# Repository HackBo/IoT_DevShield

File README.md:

# A Developement Shield for IoT proyects

A shield that include Sensors, Actuators And Comm Modules 'ready to work'.

The shield use the 'Arduino Socket' that accomplish the compatibility not only with Arduino boards also many other boards that use the 
same 'Arduino Socket' form.

The list of the actual components are:

## Sensors
 
 * MMA8452Q (Accelerometer)
 * LM35 (Temperature)
 * DHT11* (Humidity And Temperature)
 * SS39AT (Hall Effect)
 * SS351AT (Hall Effect)
 * LDR (Light)
 * Potenciometer
 * Switch

## Actuators

 * RGB LED
 * Buzzer
 * Rele
 * High Power Mosfet
 * Servo Motor*
 * LCD OLED*

## COMM Modules

 * HC05 (Bluetooth)
 * TSOP(IR Rx)
 * IR LED (IR Tx)
 * ESP-01* (WiFi)
 * NRF24L01+* (2.4GHz RF)

## Others

 * 24LC256 (EEPROM 256Kb)
 * DS1307 (RTC)

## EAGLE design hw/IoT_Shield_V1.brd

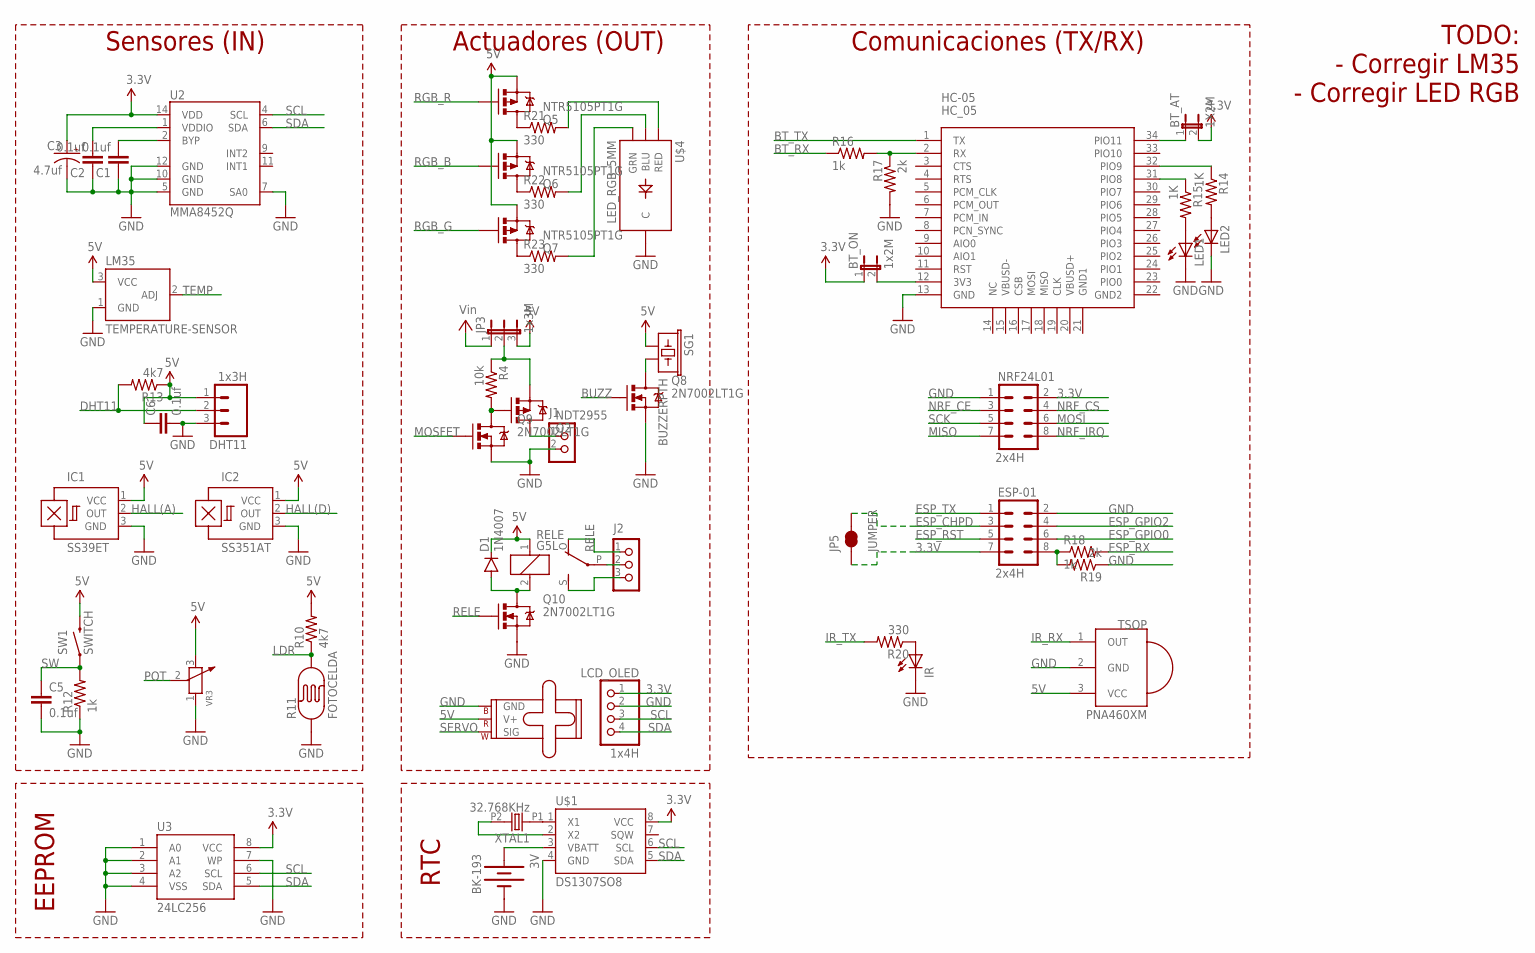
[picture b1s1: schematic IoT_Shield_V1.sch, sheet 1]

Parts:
3V: BK-193; BATTERY-20MMTH
BT_AT: 1X2M; JP1
BT_ON: 1x2M; JP1
C1, C2, C5, C6: 0.1uf; 0805
C3: 4.7uf; EIA3528-KIT
D1: 1N4007; SMA-DIODE
DHT11: 1x3H; 1X03_LOCK
ESP-01: 2x4H; 2X4
HC-05: HC_05; BLUETOOTH_SMD
IC1: SS39ET; SOT23-W
IC2: SS351AT; SOT23-W
IR: LEDIRL80A; IRL80A
J1: CON_TERMINAL_BLOCK_02-5MM; TERMINAL_BLOCK_2P_5
J2: CON_TERMINAL_BLOCK_03-5MM; TERMINAL_BLOCK_3P_5
JP3: 1x3M; JP2
JP5: JUMPER; PAD-JUMPER-2-NC_BY_TRACE_NO_SILK
LCD_OLED: 1x4H; 1X04
LED1, LED2: LEDCHIPLED_0805; CHIPLED_0805
LM35: TEMPERATURE-SENSOR; TO-92
NRF24L01: 2x4H; 2X4
Q2: NDT2955; SOT223
Q5, Q6, Q7: NTR5105PT1G; SOT23-3
Q8, Q9, Q10: 2N7002LT1G; SOT23-3
R4: 10k; 0805
R10, R13: 4k7; 0805
R11: FOTOCELDA; PHOTOCELL
R12, R16, R18: 1k; 0805
R14, R15: 1K; 0805
R17, R19: 2k; 0805
R20, R21, R22, R23: 330; 1206
RELE: G5L; G5LE
SERVO: 1X3M; 1X03
SG1: BUZZERPTH; BUZZER-12MM
SW1: SWITCH; TACTILE-PTH
TSOP: PNA460XM
U2: MMA8452Q; QFN-16_0.5MM
U3: 24LC256; SO08
U$1: DS1307SO8; SO08
U$4: LED_RGB_5MM; LED_PIRANHA_5MM
VR3: RES-ADJ'WH121-1'; ADJR2+3P-16.0X12.0X18.0MM
XTAL1: 32.768KHz; TC-26

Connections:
3.3V: BT_AT.2, BT_ON.1, C3.A (+), ESP-01.7, JP5.1, LCD_OLED.1, NRF24L01.2, U2.14 (VDD), U3.8 (VCC), U$1.8 (VCC); also elsewhere on the board
5V: C6.1, D1.C, DHT11.1, IC1.1 (VCC), IC2.1 (VCC), JP3.3, LM35.3 (VCC), Q5.2 (S), Q6.2 (S), Q7.2 (S), R10.2, R13.1, RELE.1, SERVO.2 (V+), SG1.+ (1), SW1.3 (2), TSOP.3 (VCC), VR3.3; also elsewhere on the board
BT_RX: R16.1; also elsewhere on the board
BT_TX: HC-05.1 (TX); also elsewhere on the board
BUZZ: Q8.1 (G); also elsewhere on the board
DHT11: DHT11.2, R13.2; also elsewhere on the board
ESP_CHPD: ESP-01.3, JP5.2; also elsewhere on the board
ESP_GPIO0: ESP-01.6; also elsewhere on the board
ESP_GPIO2: ESP-01.4; also elsewhere on the board
ESP_RST: ESP-01.5; also elsewhere on the board
ESP_RX: R18.2; also elsewhere on the board
ESP_TX: ESP-01.1; also elsewhere on the board
GND: 3V.P1- (-), C1.1, C2.1, C3.C (-), C5.2, C6.2, DHT11.3, ESP-01.2, HC-05.13 (GND), IC1.3 (GND), IC2.3 (GND), IR.K (C), J1.2, LCD_OLED.2, LED1.C, LED2.C, LM35.1 (GND), NRF24L01.1, Q8.2 (S), Q9.2 (S), Q10.2 (S), R11.1, R12.1, R17.2, R19.1, SERVO.3 (GND), TSOP.2 (GND), U2.5 (GND), U2.7 (SA0), U2.10 (GND), U2.12 (GND), U3.1 (A0), U3.2 (A1), U3.3 (A2), U3.4 (VSS), U3.7 (WP), U$1.4 (GND), U$4.- (C), VR3.1; also elsewhere on the board
HALL(A): IC1.2 (OUT); also elsewhere on the board
HALL(D): IC2.2 (OUT); also elsewhere on the board
IR_RX: TSOP.1 (OUT); also elsewhere on the board
IR_TX: R20.2; also elsewhere on the board
LDR: R10.1, R11.2; also elsewhere on the board
MISO: NRF24L01.7; also elsewhere on the board
MOSFET: Q9.1 (G); also elsewhere on the board
MOSI: NRF24L01.6; also elsewhere on the board
unnamed: U$1.2 (X2), XTAL1.P2 (2)
unnamed: U$1.1 (X1), XTAL1.P1 (1)
unnamed: 3V.P2+ (+), 3V.P3+ (+), U$1.3 (VBATT)
unnamed: C1.2, U2.2 (BYP)
unnamed: C2.2, U2.1 (VDDIO)
unnamed: J1.1, Q2.2 (D), Q2.4 (D)
unnamed: Q8.3 (D), SG1.- (2)
unnamed: Q2.1 (G), Q9.3 (D), R4.2
unnamed: D1.A, Q10.3 (D), RELE.2
unnamed: R23.2, U$4.G (GRN)
unnamed: R22.2, U$4.B (BLU)
unnamed: R21.2, U$4.R (RED)
unnamed: JP3.2, Q2.3 (S), R4.1
unnamed: BT_ON.2, HC-05.12 (3V3)
unnamed: HC-05.32 (PIO9), R14.1
unnamed: HC-05.31 (PIO8), R15.1
unnamed: LED1.A, R15.2
unnamed: LED2.A, R14.2
unnamed: HC-05.2 (RX), R16.2, R17.1
unnamed: ESP-01.8, R18.1, R19.2
unnamed: Q5.3 (D), R21.1
unnamed: BT_AT.1, HC-05.34 (PIO11)
unnamed: Q6.3 (D), R22.1
unnamed: Q7.3 (D), R23.1
unnamed: IR.A, R20.1
NRF_CE: NRF24L01.3; also elsewhere on the board
NRF_CS: NRF24L01.4; also elsewhere on the board
NRF_IRQ: NRF24L01.8
POT: VR3.2; also elsewhere on the board
RELE: Q10.1 (G); also elsewhere on the board
RELE_COMM: J2.2, RELE.P
RELE_NC: J2.1, RELE.O
RELE_NO: J2.3, RELE.S
RGB_B: Q6.1 (G); also elsewhere on the board
RGB_G: Q7.1 (G); also elsewhere on the board
RGB_R: Q5.1 (G); also elsewhere on the board
SCK: NRF24L01.5; also elsewhere on the board
SCL: LCD_OLED.3, U2.4 (SCL), U3.6 (SCL), U$1.6 (SCL); also elsewhere on the board
SDA: LCD_OLED.4, U2.6 (SDA), U3.5 (SDA), U$1.5 (SDA); also elsewhere on the board
SERVO: SERVO.1 (SIG); also elsewhere on the board
SW: C5.1, R12.2, SW1.1; also elsewhere on the board
TEMP: LM35.2 (ADJ); also elsewhere on the board
VIN: JP3.1; also elsewhere on the board

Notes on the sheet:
Sensores (IN)
Actuadores (OUT)
Comunicaciones (TX/RX)
RTC
EEPROM
TODO: - Corregir LM35 - Corregir LED RGB

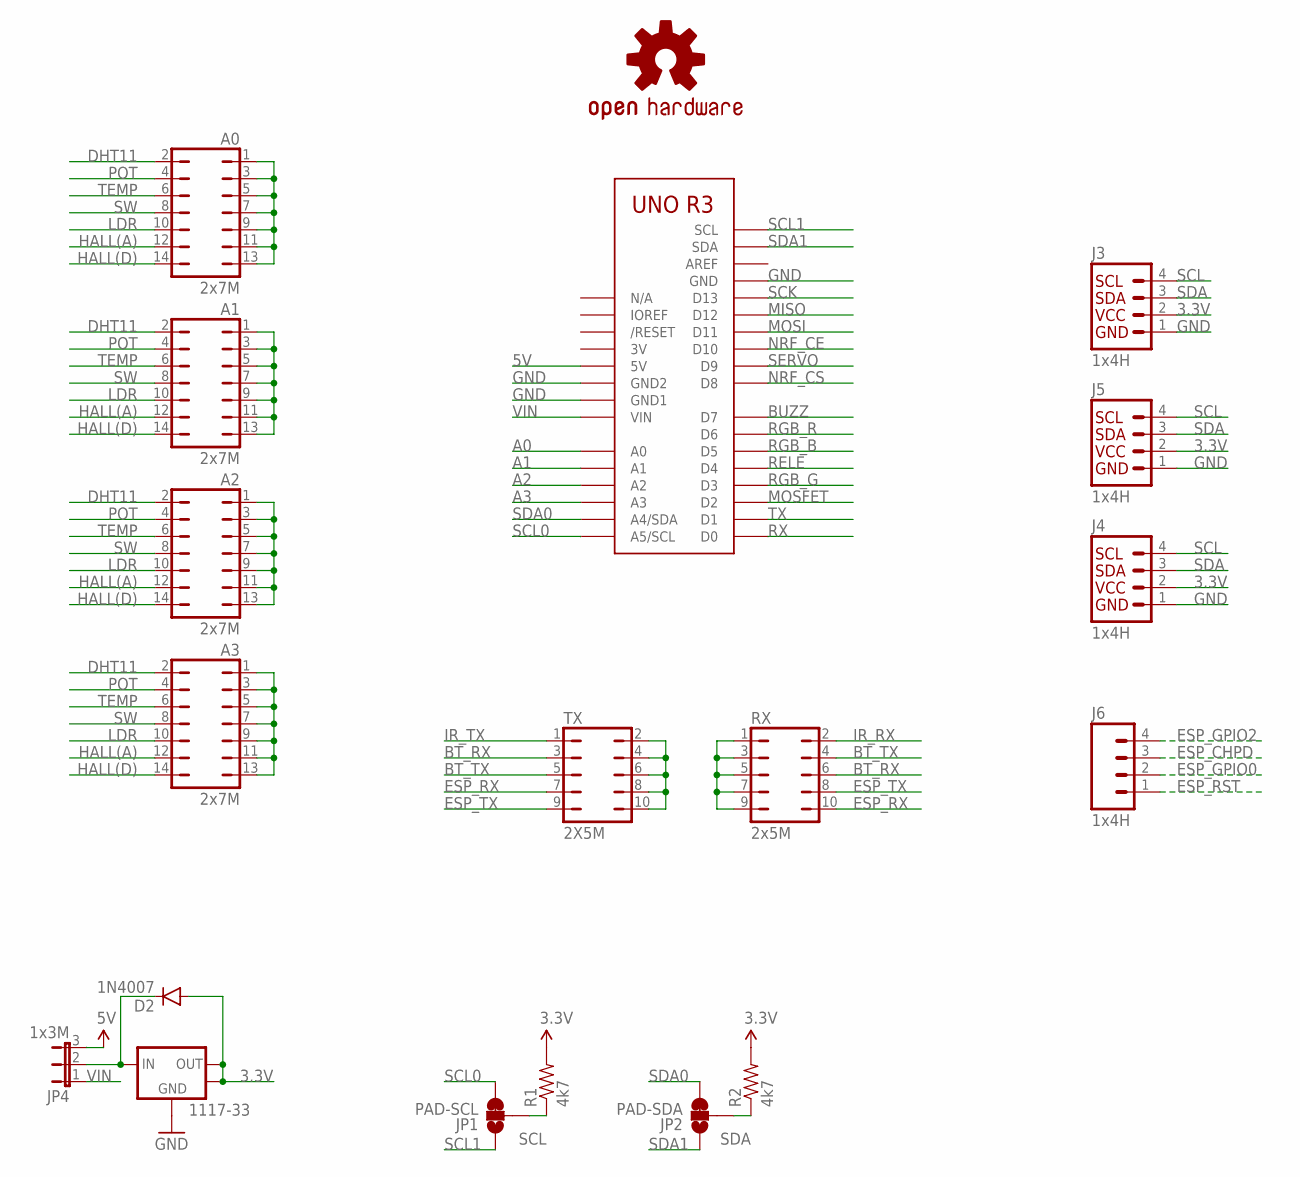
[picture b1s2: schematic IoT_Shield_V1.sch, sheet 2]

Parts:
1117-33: LV1117-33TO252; TO252
A0, A1, A2, A3: 2x7M; JP7Q
D2: 1N4007; SMA-DIODE
J3, J4, J5: 1x4H; 1X04
J6: 1x4H; 1X04_LOCK
JP1: PAD-SCL; PAD-JUMPER-3-2OF3_NC_BY_TRACE_YES_SILK_LARGE
JP2: PAD-SDA; PAD-JUMPER-3-2OF3_NC_BY_TRACE_YES_SILK_LARGE
JP4: 1x3M; JP2
LOGO1: OSHW-LOGOL-COPPER; OSHW-LOGO-L_COPPER
R1, R2: 4k7; 0805
RX: 2x5M; JP5Q
TX: 2X5M; JP5Q
U1: ARDUINOR3-DIMENSION; ARDUINOR3

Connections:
3.3V: 1117-33.2 (OUT), 1117-33.4 (OUT), D2.A, J3.2, J4.2, J5.2, R1.2, R2.2; also elsewhere on the board
3V: U1.3V
5V: JP4.3, U1.5V; also elsewhere on the board
A0: A0.1, A0.3, A0.5, A0.7, A0.9, A0.11, A0.13, U1.A0
A1: A1.1, A1.3, A1.5, A1.7, A1.9, A1.11, A1.13, U1.A1
A2: A2.1, A2.3, A2.5, A2.7, A2.9, A2.11, A2.13, U1.A2
A3: A3.1, A3.3, A3.5, A3.7, A3.9, A3.11, A3.13, U1.A3
BT_RX: RX.6, TX.3; also elsewhere on the board
BT_TX: RX.4, TX.5; also elsewhere on the board
BUZZ: U1.D7; also elsewhere on the board
DHT11: A0.2, A1.2, A2.2, A3.2; also elsewhere on the board
ESP_CHPD: J6.3; also elsewhere on the board
ESP_GPIO0: J6.2; also elsewhere on the board
ESP_GPIO2: J6.4; also elsewhere on the board
ESP_RST: J6.1; also elsewhere on the board
ESP_RX: RX.10, TX.7; also elsewhere on the board
ESP_TX: RX.8, TX.9; also elsewhere on the board
GND: 1117-33.1 (ADJ), J3.1, J4.1, J5.1, U1.GND, U1.GND1, U1.GND2; also elsewhere on the board
HALL(A): A0.12, A1.12, A2.12, A3.12; also elsewhere on the board
HALL(D): A0.14, A1.14, A2.14, A3.14; also elsewhere on the board
IR_RX: RX.2; also elsewhere on the board
IR_TX: TX.1; also elsewhere on the board
LDR: A0.10, A1.10, A2.10, A3.10; also elsewhere on the board
MISO: U1.D12; also elsewhere on the board
MOSFET: U1.D2; also elsewhere on the board
MOSI: U1.D11; also elsewhere on the board
unnamed: 1117-33.3 (IN), D2.C, JP4.2
NRF_CE: U1.D10; also elsewhere on the board
NRF_CS: U1.D8; also elsewhere on the board
POT: A0.4, A1.4, A2.4, A3.4; also elsewhere on the board
RELE: U1.D4; also elsewhere on the board
RGB_B: U1.D5; also elsewhere on the board
RGB_G: U1.D3; also elsewhere on the board
RGB_R: U1.D6; also elsewhere on the board
RX: RX.1, RX.3, RX.5, RX.7, RX.9, U1.D0
SCK: U1.D13; also elsewhere on the board
SCL: J3.4, J4.4, J5.4, JP1.2, R1.1; also elsewhere on the board
SCL0: JP1.3, U1.A5 (A5/SCL)
SCL1: JP1.1, U1.SCL
SDA: J3.3, J4.3, J5.3, JP2.2, R2.1; also elsewhere on the board
SDA0: JP2.3, U1.A4 (A4/SDA)
SDA1: JP2.1, U1.SDA
SERVO: U1.D9; also elsewhere on the board
SW: A0.8, A1.8, A2.8, A3.8; also elsewhere on the board
TEMP: A0.6, A1.6, A2.6, A3.6; also elsewhere on the board
TX: TX.2, TX.4, TX.6, TX.8, TX.10, U1.D1
VIN: JP4.1, U1.VIN; also elsewhere on the board

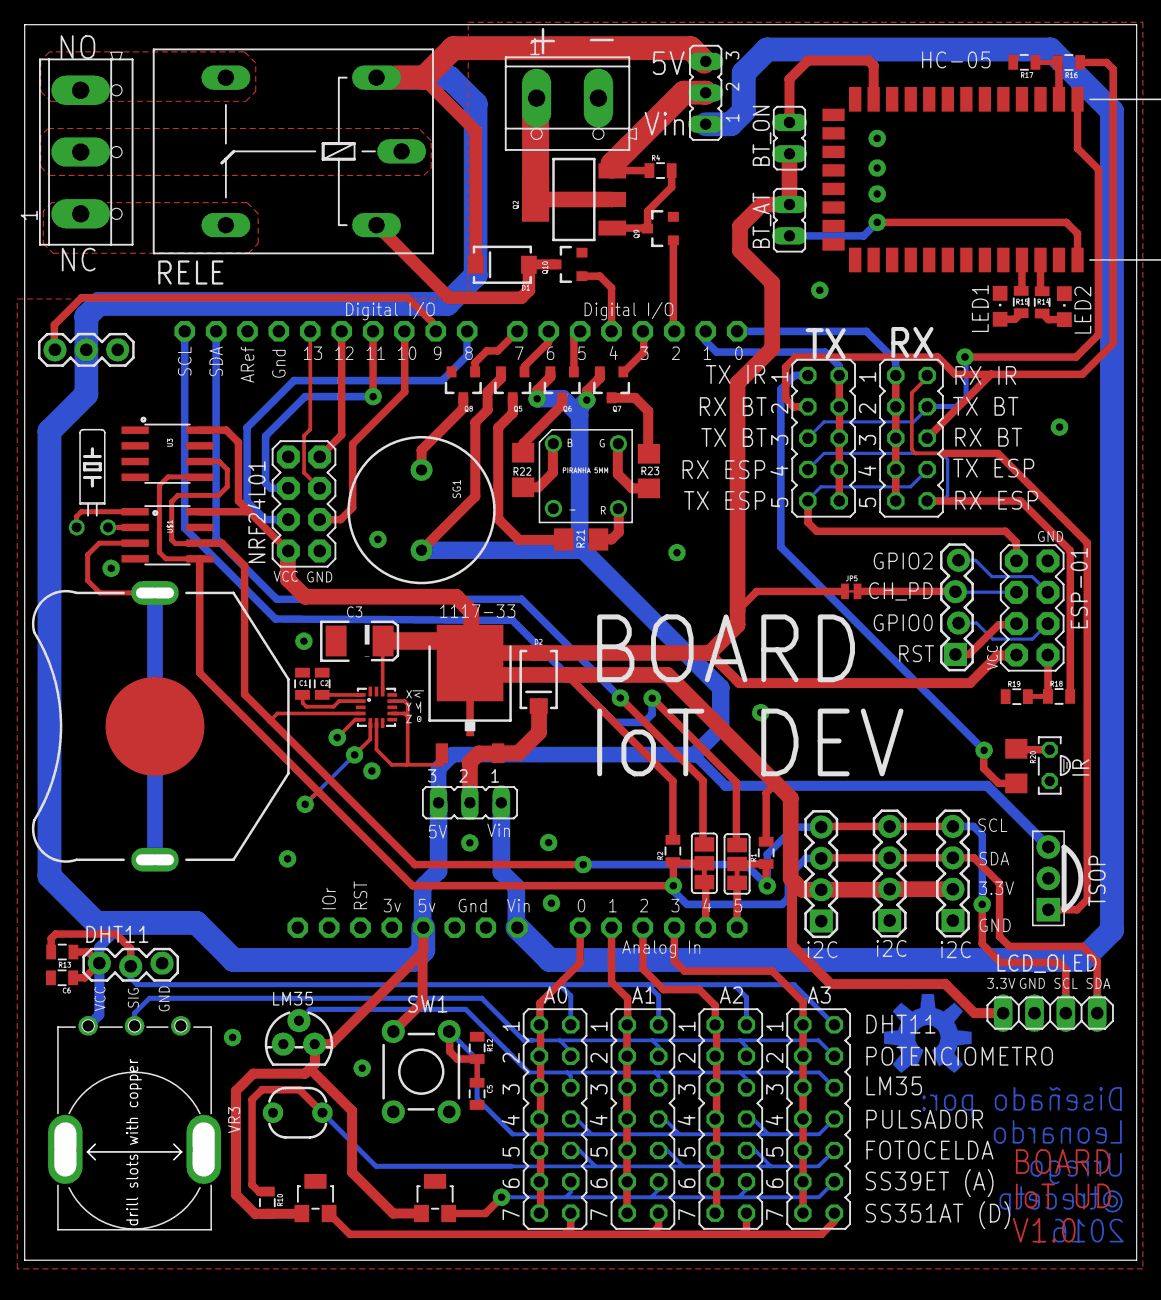
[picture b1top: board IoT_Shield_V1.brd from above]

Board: 2 copper layers, 88.2 x 99.4 mm, 76 parts (1 on the bottom side), 74 nets.

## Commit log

2017-03-15 First Version
2017-03-16 Add Readme
2017-05-10 Algunas imagenes de Archivo
2017-05-10 Codigo de ejemplo para probar la tarjeta

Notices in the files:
parts and their libraries:
SparkFun-Capacitors: Licensing: Creative Commons ShareAlike 4.0 International - https://creativecommons.org/licenses/by-sa/4.0
